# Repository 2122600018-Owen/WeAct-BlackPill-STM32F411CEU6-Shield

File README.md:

# WeAct-BlackPill-STM32F411CEU6-Shield
Multipurpose Testing Shield for WeAct STM32F411CEU6 Board

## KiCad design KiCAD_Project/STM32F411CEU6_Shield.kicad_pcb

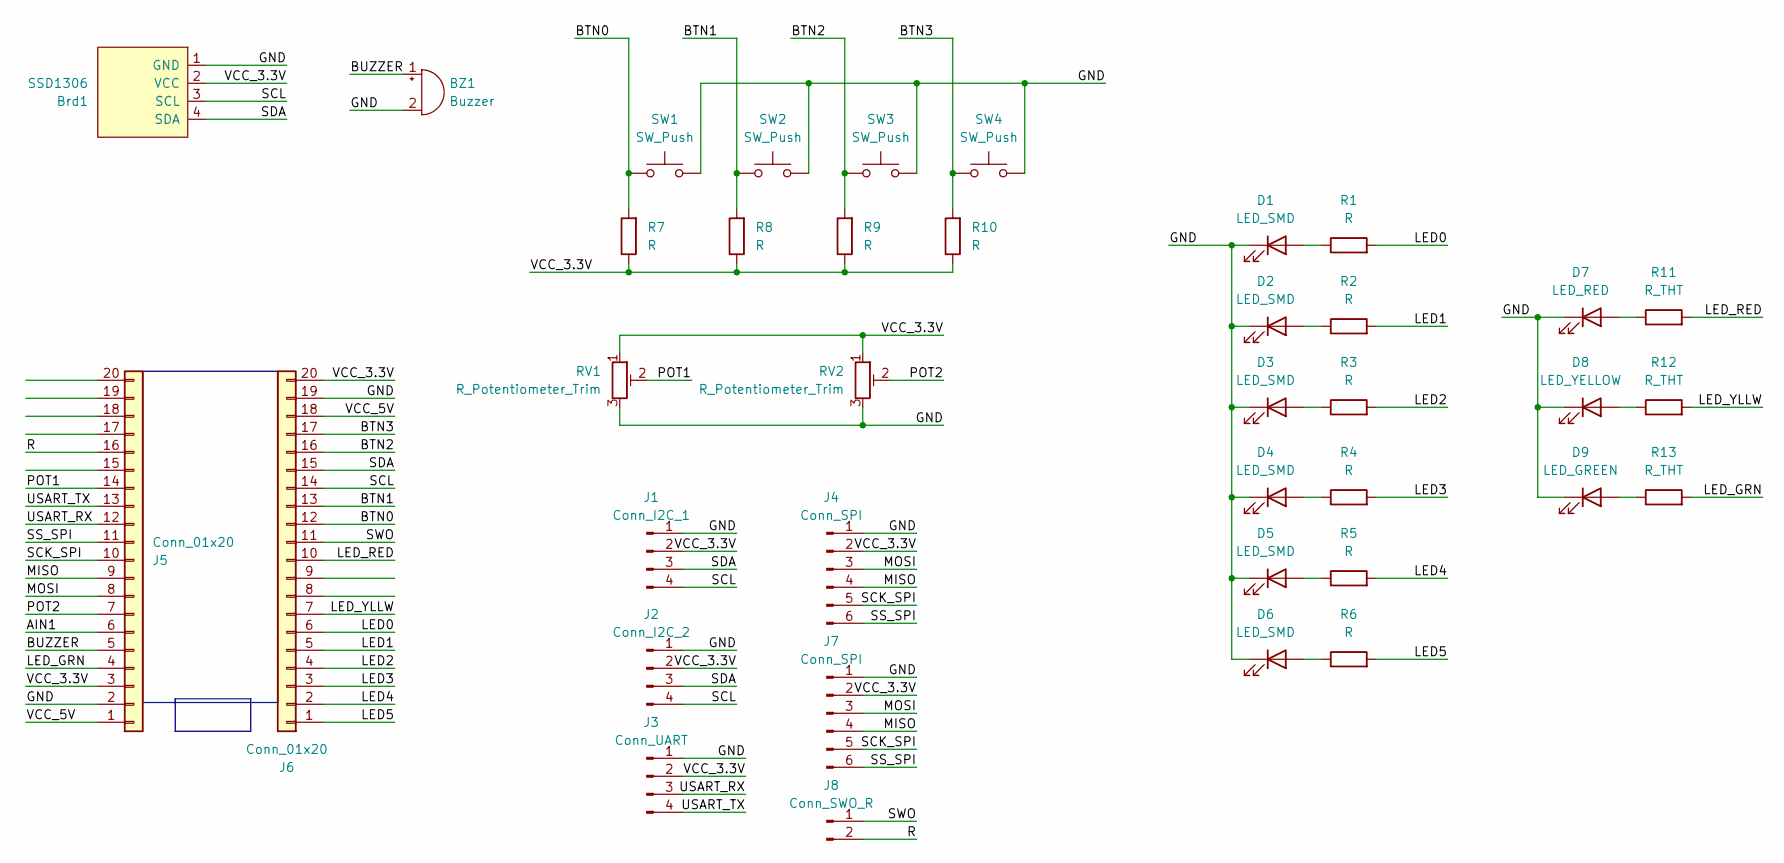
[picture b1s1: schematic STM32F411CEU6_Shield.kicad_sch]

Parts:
BZ1: Buzzer; Buzzer_12x9.5RM7.6
Brd1: SSD1306; 128x64OLED
D1, D2, D3, D4, D5, D6: LED_SMD; LED_1206_3216Metric_Pad1.42x1.75mm_HandSolder
D7: LED_RED; LED_D3.0mm
D8: LED_YELLOW; LED_D3.0mm
D9: LED_GREEN; LED_D3.0mm
J1: Conn_I2C_1; PinHeader_1x04_P2.54mm_Vertical
J2: Conn_I2C_2; PinHeader_1x04_P2.54mm_Vertical
J3: Conn_UART; PinHeader_1x04_P2.54mm_Vertical
J4, J7: Conn_SPI; PinHeader_1x06_P2.54mm_Vertical
J5, J6: Conn_01x20; PinSocket_1x20_P2.54mm_Vertical
J8: Conn_SWO_R; PinSocket_1x02_P2.54mm_Vertical
R1, R2, R3, R4, R5, R6, R7, R8, R9, R10: R; R_1206_3216Metric_Pad1.30x1.75mm_HandSolder
R11, R12, R13: R_THT; R_Axial_DIN0207_L6.3mm_D2.5mm_P10.16mm_Horizontal
RV1, RV2: R_Potentiometer_Trim; Potentiometer_Runtron_RM-065_Vertical
SW1, SW2, SW3, SW4: SW_Push; SW_PUSH_6mm

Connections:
/AIN1: J5.6
/BTN0: J6.12, R7.2, SW1.1
/BTN1: J6.13, R8.2, SW2.1
/BTN2: J6.16, R9.2, SW3.1
/BTN3: J6.17, R10.2, SW4.1
/BUZZER: BZ1.1 (+), J5.5
/GND: BZ1.2 (-), Brd1.1 (GND), D1.1 (K), D2.1 (K), D3.1 (K), D4.1 (K), D5.1 (K), D6.1 (K), D7.1 (K), D8.1 (K), D9.1 (K), J1.1, J2.1, J3.1, J4.1, J5.2, J6.19, J7.1, RV1.3, RV2.3, SW1.2, SW2.2, SW3.2, SW4.2
/LED0: J6.6, R1.2
/LED1: J6.5, R2.2
/LED2: J6.4, R3.2
/LED3: J6.3, R4.2
/LED4: J6.2, R5.2
/LED5: J6.1, R6.2
/LED_GRN: J5.4, R13.2
/LED_RED: J6.10, R11.2
/LED_YLLW: J6.7, R12.2
/MISO: J4.4, J5.9, J7.4
/MOSI: J4.3, J5.8, J7.3
/POT1: J5.14, RV1.2
/POT2: J5.7, RV2.2
/R: J5.16, J8.2
/SCK_SPI: J4.5, J5.10, J7.5
/SCL: Brd1.3 (SCL), J1.4, J2.4, J6.14
/SDA: Brd1.4 (SDA), J1.3, J2.3, J6.15
/SS_SPI: J4.6, J5.11, J7.6
/SWO: J6.11, J8.1
/USART_RX: J3.3, J5.12
/USART_TX: J3.4, J5.13
/VCC_3.3V: Brd1.2 (VCC), J1.2, J2.2, J3.2, J4.2, J5.3, J6.20, J7.2, R7.1, R8.1, R9.1, R10.1, RV1.1, RV2.1
/VCC_5V: J5.1, J6.18
unnamed: D1.2 (A), R1.1
unnamed: D2.2 (A), R2.1
unnamed: D3.2 (A), R3.1
unnamed: D4.2 (A), R4.1
unnamed: D5.2 (A), R5.1
unnamed: D6.2 (A), R6.1
unnamed: D7.2 (A), R11.1
unnamed: D8.2 (A), R12.1
unnamed: D9.2 (A), R13.1

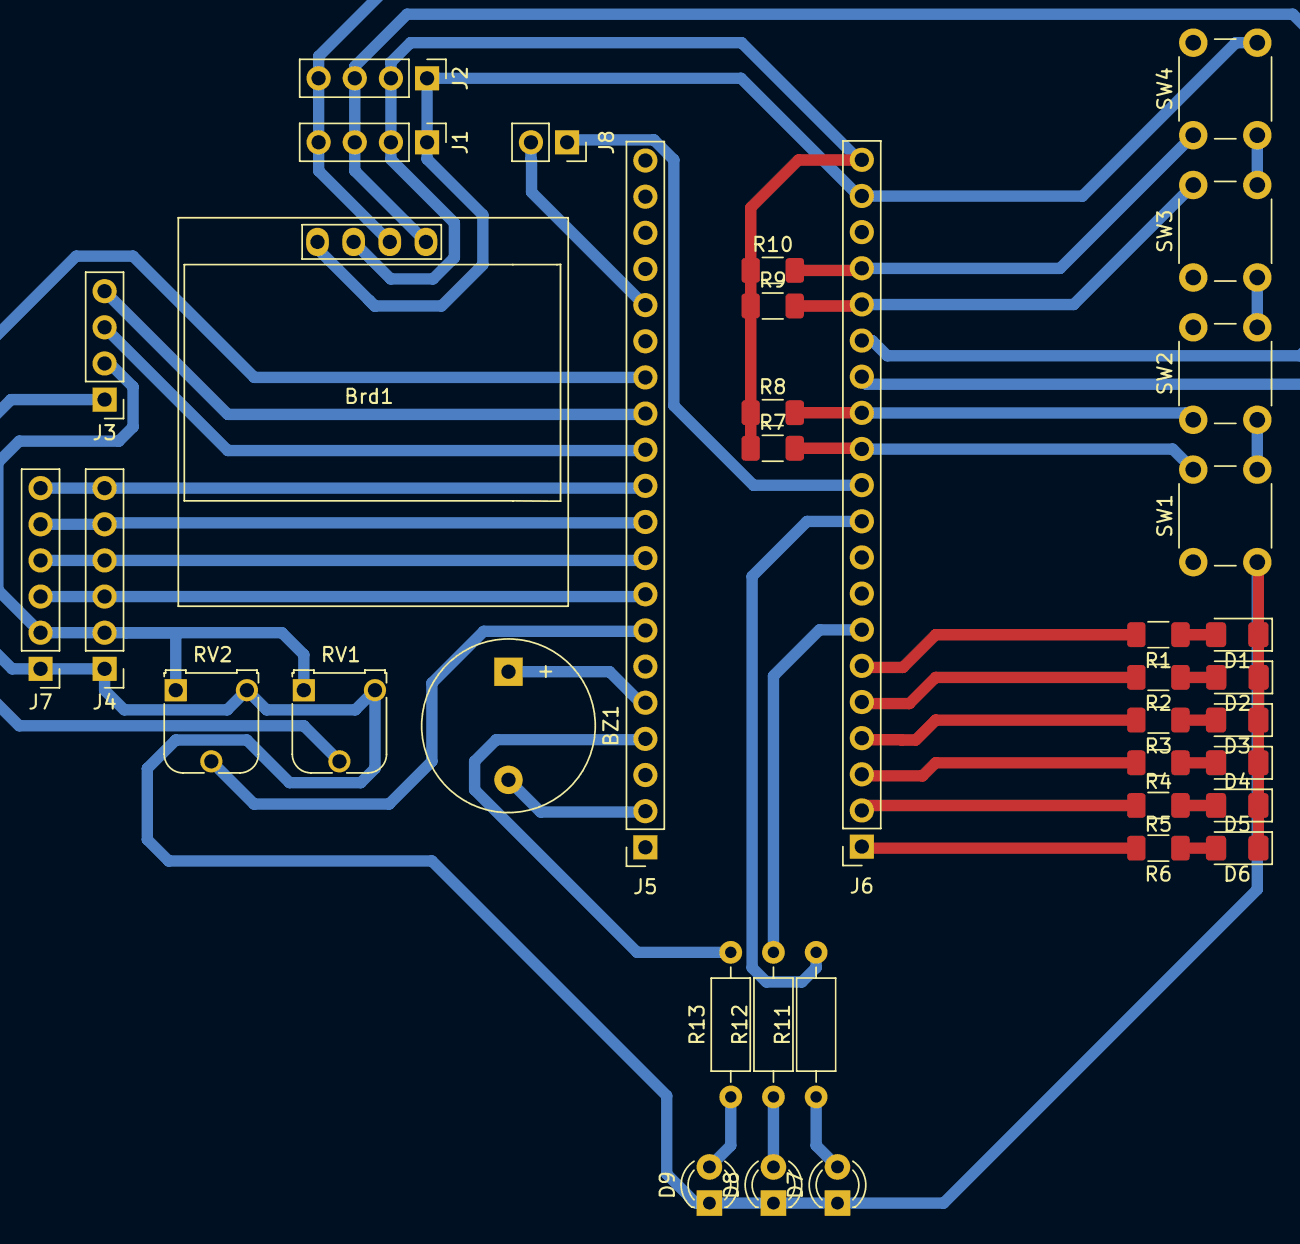
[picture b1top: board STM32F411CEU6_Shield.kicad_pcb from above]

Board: 2 copper layers, 38 parts (0 on the bottom side), 38 nets.

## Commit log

2024-11-08 Create a
2024-11-08 Added PCB, Schematic, and KiCAD Project Files
